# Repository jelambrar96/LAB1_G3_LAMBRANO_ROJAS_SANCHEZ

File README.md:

# LAB1_G3_LAMBRANO_ROJAS_SANCHEZ

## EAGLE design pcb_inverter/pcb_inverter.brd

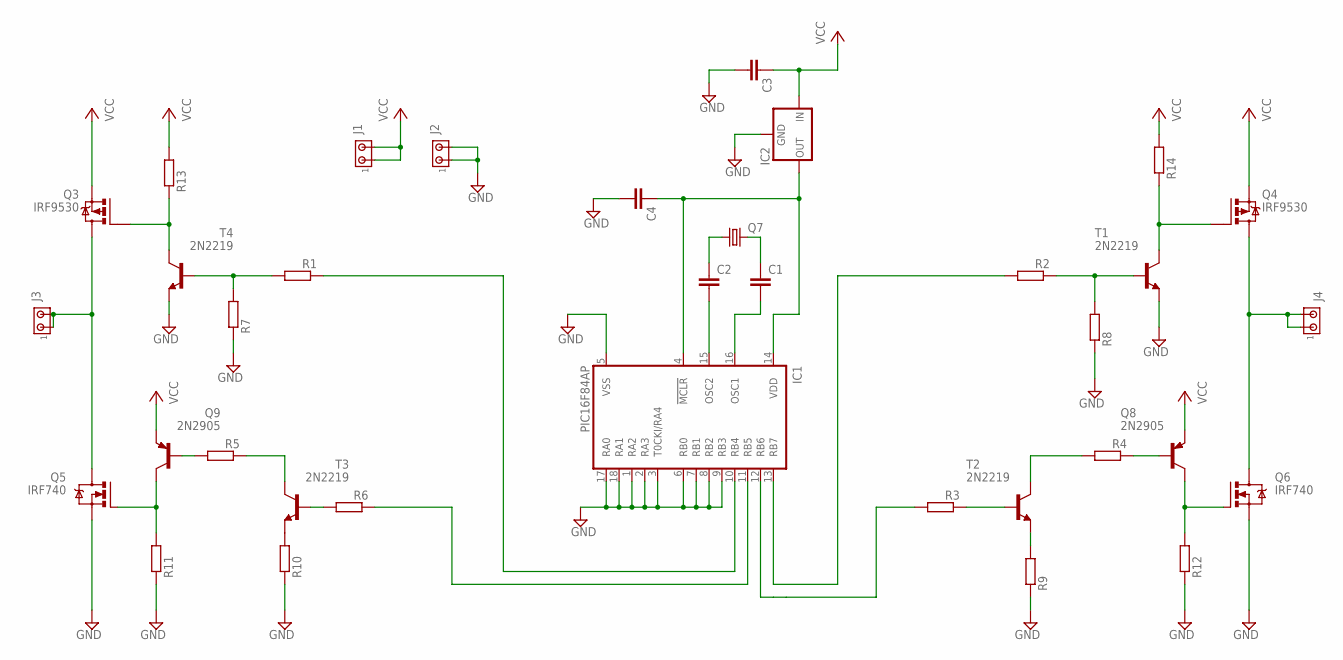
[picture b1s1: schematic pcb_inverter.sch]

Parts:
C1, C2, C3, C4: C2.5/5; C2.5-5
IC1: PIC16F84AP; DIL18
IC2: 78XXS
J1, J2, J3, J4: MTA02-156; 1X2MTA
Q3, Q4: IRF9530; TO220BV
Q5, Q6: IRF740; TO220BV
Q7: CRYSTALHC18U-V; HC18U-V
Q8, Q9: 2N2905; TO5
R1, R2, R3, R4, R5, R6, R7, R8, R9, R10, R11, R12, R13, R14: R-EU_0204/7; 0204/7
T1, T2, T3, T4: 2N2219; TO5

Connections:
GND: C3.2, C4.2, IC1.1 (RA2), IC1.2 (RA3), IC1.3 (T0CKI/RA4), IC1.5 (VSS), IC1.6 (RB0), IC1.7 (RB1), IC1.8 (RB2), IC1.9 (RB3), IC1.17 (RA0), IC1.18 (RA1), IC2.GND, J2.1, J2.2, Q5.S, Q6.S, R7.1, R8.1, R9.1, R10.1, R11.1, R12.1, T1.1 (E), T4.1 (E)
unnamed: Q3.G, R13.1, T4.3 (C)
unnamed: R1.2, R7.2, T4.2 (B)
unnamed: J3.1, J3.2, Q3.D, Q5.D
unnamed: Q6.G, Q8.3 (C), R12.2
unnamed: Q5.G, Q9.3 (C), R11.2
unnamed: Q9.2 (B), R5.2
unnamed: R5.1, T3.3 (C)
unnamed: R10.2, T3.1 (E)
unnamed: R6.2, T3.2 (B)
unnamed: IC1.11 (RB5), R6.1
unnamed: Q8.2 (B), R4.1
unnamed: R4.2, T2.3 (C)
unnamed: R9.2, T2.1 (E)
unnamed: R3.1, T2.2 (B)
unnamed: IC1.10 (RB4), R1.1
unnamed: J4.1, J4.2, Q4.D, Q6.D
unnamed: Q4.G, R14.1, T1.3 (C)
unnamed: R2.1, R8.2, T1.2 (B)
unnamed: C2.1, Q7.1
unnamed: C2.2, IC1.15 (OSC2)
unnamed: C1.2, IC1.16 (OSC1)
unnamed: C1.1, Q7.2
unnamed: IC1.12 (RB6), R3.2
unnamed: IC1.13 (RB7), R2.2
unnamed: C4.1, IC1.4 (!MCLR), IC1.14 (VDD), IC2.OUT
VCC: C3.1, IC2.IN, J1.1, J1.2, Q3.S, Q4.S, Q8.1 (E), Q9.1 (E), R13.2, R14.2

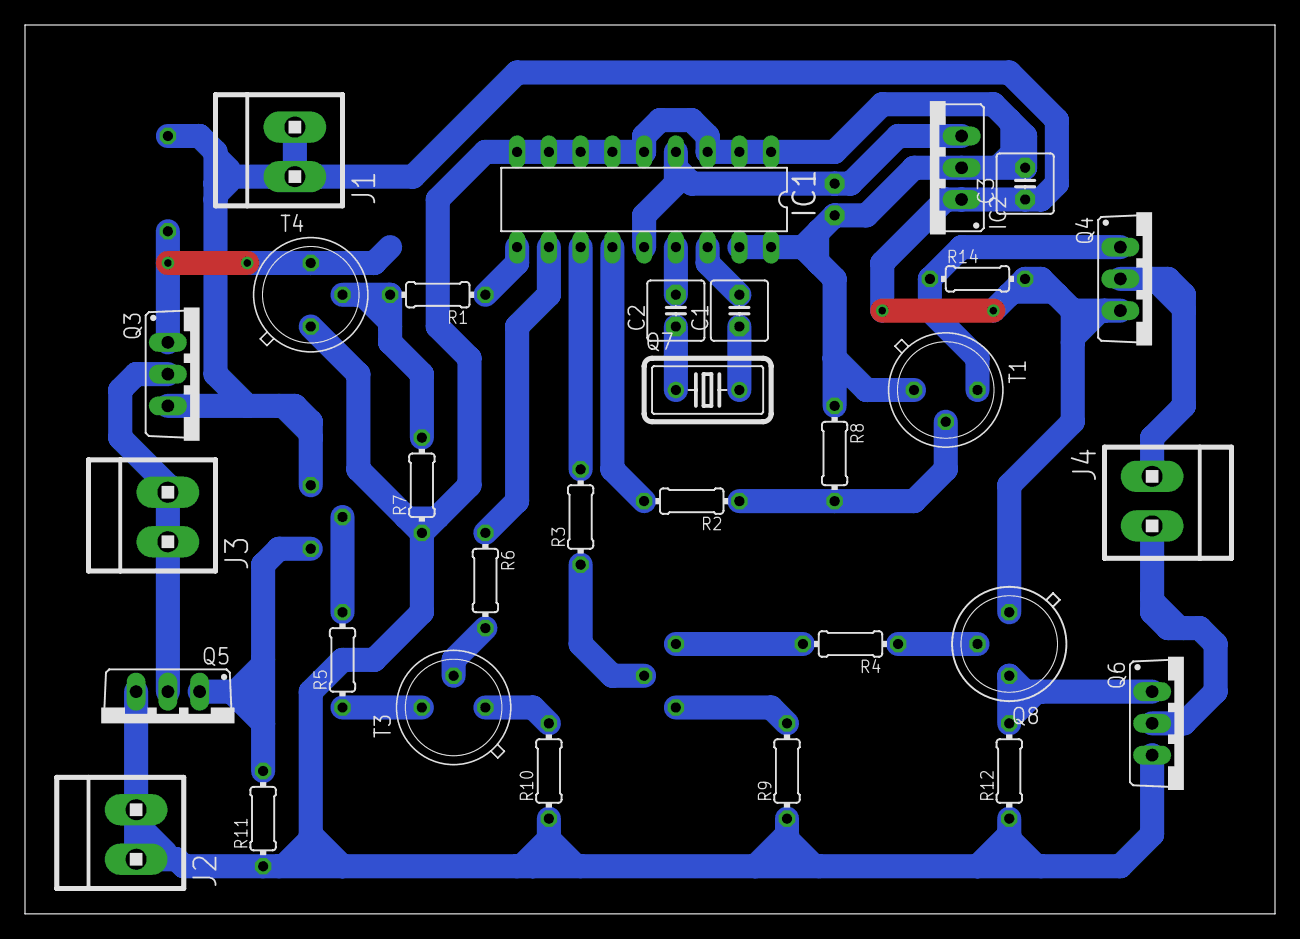
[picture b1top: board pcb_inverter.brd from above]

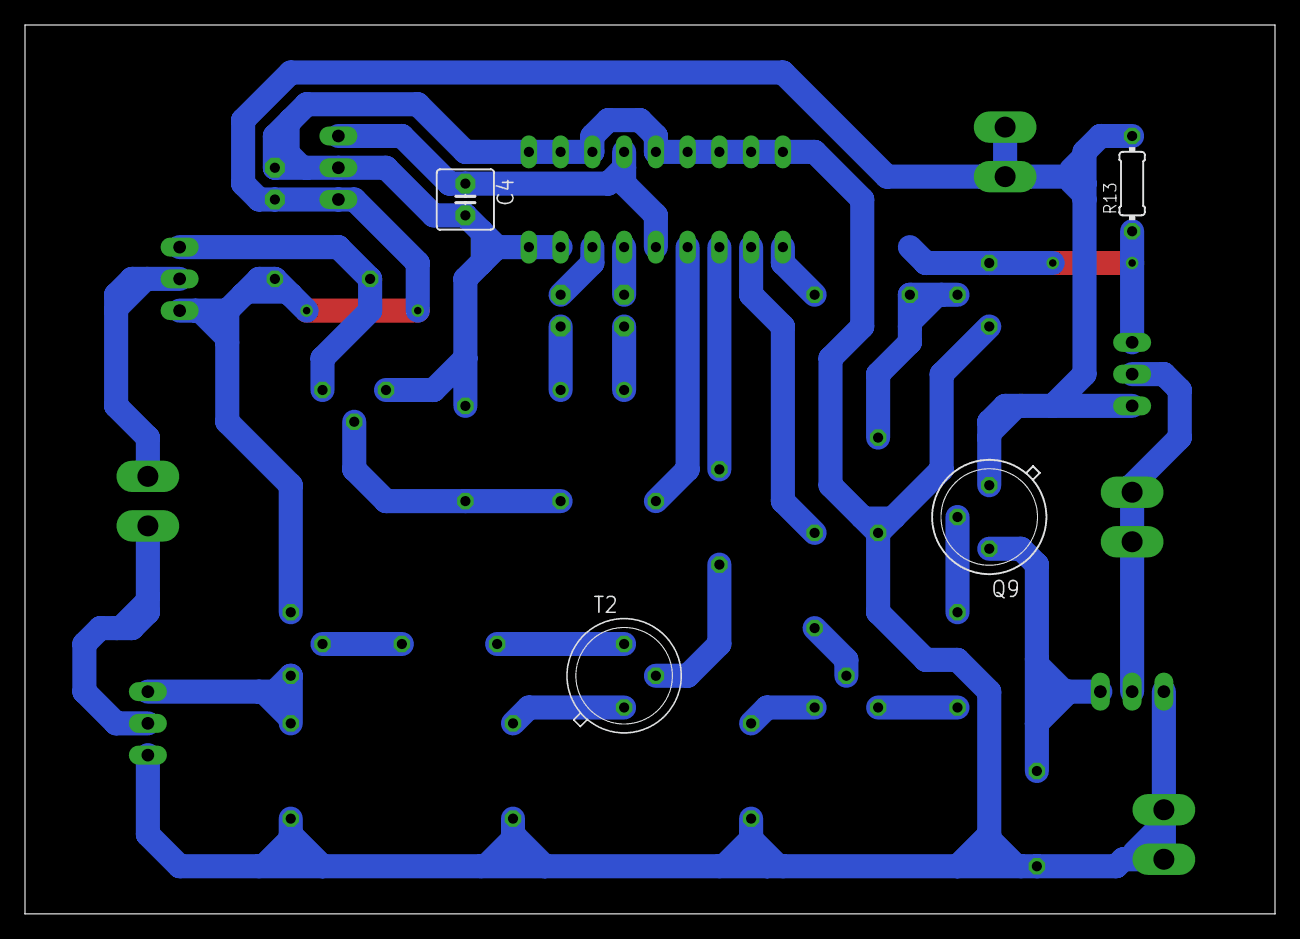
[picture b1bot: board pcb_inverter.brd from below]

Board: 2 copper layers, 100.0 x 71.1 mm, 35 parts (4 on the bottom side), 27 nets.

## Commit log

2018-04-24 simulation added
2018-04-24 .gitignore added
2018-05-14 jela
